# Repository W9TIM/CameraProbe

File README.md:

# CameraProbe

A macOS menu bar utility that watches for camera activity and reacts to it: flips a physical "on air" relay, and/or fires a Home Assistant webhook, whenever your Mac's camera turns on or off.

Ships as a normal `.app` you drag into `/Applications` - no installer, no `sudo`, no LaunchAgent. It lives in the menu bar with a custom tally-light icon, shows a red dot on top of it whenever the camera is actively in use, and everything is configured from a Preferences window.

> **Windows:** a Windows 10/11 tray version (2.0.0, matching this macOS release) lives in [`windows/`](windows/README.md). It uses the same relay firmware, Home Assistant webhooks and config schema. The rest of this README covers the macOS app.

## Features

- Detects camera start/stop by watching the unified log stream for `cameracaptured` events - no polling, no private APIs.
- Reports which application grabbed the camera (Zoom, FaceTime, Photo Booth, Teams, browsers, etc.).
- Controls an HTTP-controlled relay (e.g. an ESP8266/ESP32 running Tasmota or custom firmware) for a physical "on air" light.
- Fires Home Assistant webhooks (`camera_on` / `camera_off`) so you can build automations on top of camera state.
- Menu bar icon shows a red dot the instant CameraProbe itself detects the camera in use by a non-excluded app - a local, independent signal that doesn't depend on the relay or Home Assistant being enabled, configured, or reachable. Goes dark while Inactivate is on.
- Right-click menu: About, Preferences, Inactivate/Reactivate (pause relay + Home Assistant notifications without quitting - camera detection keeps running), Quit.
- Preferences window for relay, Home Assistant, ignored apps, and Start at Login - no manual config-file editing required. Changes apply immediately, no restart.
- `ignoredApplications` exclude list - apps that activate the camera without ever notifying the relay/Home Assistant (privacy, gameplay capture, etc.), editable from Preferences.
- Self-healing: if the underlying log-stream process dies, it restarts automatically with backoff.
- `CameraProbe --test` and `CameraProbe --status` for command-line diagnostics.

## Requirements

- macOS 14 or later.
- Xcode Command Line Tools (to build from source): `xcode-select --install`.
- An HTTP-controlled relay reachable on your LAN (optional - can be disabled in Preferences).
- A Home Assistant instance with webhook automations for `camera_on` / `camera_off` (optional - can be disabled in Preferences).

## Download

Prebuilt installers are on the [**latest release**](https://github.com/W9TIM/CameraProbe/releases/latest) page:

- **macOS:** `CameraProbe.dmg` - open it and drag **CameraProbe** onto **Applications**.
- **Windows:** `CameraProbe-Setup-<version>.exe` - run it (see [`windows/README.md`](windows/README.md#install)).

Neither is signed or notarized, so your OS will warn on first launch - see **First launch** below (macOS) or the Windows README (SmartScreen: **More info → Run anyway**). Prefer to build it yourself? Use the steps below.

## Install (build from source)

```
git clone <this repository>
cd CameraProbe
./build-app.sh
```

This builds the release binary and assembles `dist/CameraProbe.app` (plus `dist/CameraProbe.dmg`). No `sudo` at any point.

Then either:

- Open `dist/CameraProbe.dmg` and drag **CameraProbe** onto the **Applications** shortcut, or
- Drag `dist/CameraProbe.app` straight into `/Applications` in Finder.

**First launch:** the app isn't notarized by Apple, so right-click `CameraProbe.app` in `/Applications` and choose **Open**, then confirm - after that first approval, opening it normally (double-click, Spotlight, login item) works fine. If macOS still refuses, open **System Settings → Privacy & Security**, scroll to the message about CameraProbe, and click **Open Anyway**.

A brief splash screen (showing the app's own tally-light icon) appears, then CameraProbe settles into the menu bar (look for the tally-light icon near the clock - no Dock icon, this is a background utility). The first time it talks to the network, macOS shows a **Local Network** permission prompt - click **Allow**. `build-app.sh` code-signs the app with a stable identifier specifically so this approval survives future rebuilds.

Open the menu bar icon → **Preferences…** to set your relay and Home Assistant hostnames, and optionally turn on **Start at Login**.

See [INSTALL.md](INSTALL.md) for a more detailed walkthrough and troubleshooting.

## Configuration

Preferences window (menu bar icon → **Preferences…**) is the normal way to change settings - relay enabled/host/port, Home Assistant enabled/host/port, ignored applications, and Start at Login. Saving writes to disk and takes effect immediately, no restart needed.

Under the hood, this is stored at `~/Library/Application Support/CameraProbe/config.json`:

```json
{
  "relay": {
    "enabled": true,
    "host": "onair.local",
    "port": 80
  },
  "homeAssistant": {
    "enabled": true,
    "host": "homeassistant.local",
    "port": 8123
  },
  "ignoredApplications": []
}
```

Every field is optional - anything you omit falls back to the default shown above. You can hand-edit this file directly if you prefer (per-user path, no `sudo` needed); CameraProbe doesn't watch it for external changes, though, so use Preferences if the app is already running. A malformed config file is logged as a warning and CameraProbe falls back to defaults rather than failing to start.

**`ignoredApplications`** is an exclude list: every app that activates the camera still triggers a notification by default (empty list), but you can name specific apps to skip - for privacy (e.g. Photo Booth) or gameplay capture you don't want broadcasting "on air". Add them one per line in Preferences, or as a JSON array:

```json
"ignoredApplications": ["Photo Booth", "OBS"]
```

Matching is case-insensitive and uses the same app name CameraProbe logs/reports (`log stream --predicate 'subsystem == "com.tim.cameraprobe"'` will show you the exact name it detected if you're not sure). When an ignored app is what grabbed the camera, neither the relay nor Home Assistant gets notified for that session - including the matching "off" event, so you won't see a stray "camera off" with no preceding "on".

See `config.example.json` for a copyable template.

## Usage

CameraProbe normally just runs in the menu bar, but the same binary supports a few commands directly from Terminal (handy for scripting/troubleshooting):

```
CameraProbe                Launch the menu bar app (splash screen, then runs in the menu bar)
CameraProbe --status       One-shot summary: relay, Home Assistant, Start at Login, camera monitor
CameraProbe --test         Full diagnostics: DNS, relay, Home Assistant, log access, Start at Login
CameraProbe --version      Print the version
CameraProbe --help         Show usage
```

Example `--status` output:

```
CameraProbe 2.0.0

Relay...............OK
Home Assistant......OK
Start at Login......Enabled
Camera Monitor......Running
```

Live logs:

```
log stream --predicate 'subsystem == "com.tim.cameraprobe"'
```

## Uninstall

Turn off **Start at Login** in Preferences first (if you'd enabled it), then quit CameraProbe from the menu bar and drag `CameraProbe.app` from `/Applications` to the Trash. That's it - no installer to run in reverse.

To also remove your saved settings:

```
rm -rf ~/Library/Application\ Support/CameraProbe
```

If you're upgrading from the older LaunchAgent-based install, see the note at the top of [INSTALL.md](INSTALL.md) for how to remove that first.

## How it works

CameraProbe shells out to `/usr/bin/log stream` with a predicate that matches `cameracaptured`'s `DidStartRunning`/`DidStopRunning` events - the same signal macOS's own camera indicator light relies on. When the camera turns on, it waits briefly (to let the capturing app become frontmost), asks `NSWorkspace` which application is active, then notifies the relay and Home Assistant (unless the app is in `ignoredApplications`, or Inactivate is on). When it turns off, both get an "off" notification immediately.

The menu bar's red dot is driven by that same local detection, independently of whether the relay/Home Assistant notifications actually went out: it lights up the instant a non-excluded app grabs the camera, and goes dark the instant the camera is released or Inactivate is toggled on. It never polls or depends on the relay or Home Assistant being enabled, configured, or reachable - it's purely "does CameraProbe itself currently consider the camera in use."

## Relay firmware

The `firmware/` folder has the ESP8266 firmware for the physical relay CameraProbe talks to by default. The recommended **universal firmware** (`CameraProbeRelayUniversal/`) works on either a **Wemos D1 Mini with relay shield** or the more compact **ESP-01S relay module**. You flash it once, then set WiFi and the board type from a web page, either on the device's **ConfigRelay** setup network or at `http://onair.local/configure`. The original fixed-configuration sketches (`CameraProbeRelay/`, `CameraProbeRelay8266/`) are kept as well. See [firmware/README.md](firmware/README.md) for which to choose, wiring, Arduino IDE setup, and flashing instructions. If you already have relay hardware exposing `GET /on` / `GET /off` / `GET /status`, you don't need it; just point the relay host in Preferences (or `config.json`) at your existing device.

The low voltage relay is used for controlling power to a 5V (USB) light (On/Off) via WiFi. The control unit is constructed with a Wemos D1 Mini (ESP8266) with a single relay shield attached.

This can be housed in a simple 3D printable enclosure and mounted near or for shaddow box lights, inside to keep it out of the way. This arrangement will require two USB connections. One to power the Wemos D1 and one to power the light itself, which will be switched on/off when the +5v line is interrupted by the relay shield. 

Photos and 3D-printable files are included with this project:

- **ESP-01S relay case:** a compact two-part enclosure (base and friction-fit lid) - print-ready [STL](firmware/ESP8266%20Module%20Device/ESP01S_Relay_Case.stl), editable [OpenSCAD source](firmware/ESP8266%20Module%20Device/ESP01S_Relay_Case.scad), and the [design spec](firmware/ESP8266%20Module%20Device/CASE_DESIGN_SPEC.md). Includes a single-supply wiring photo and diagram in [firmware/README.md](firmware/README.md#single-supply-wiring-esp-01s-relay-variant).
- **Wemos D1 Mini case:** see the `3D Printable Files` folder under `firmware/`.

## Home Assistant setup

CameraProbe calls two built-in Home Assistant webhooks (`camera_on` / `camera_off`) - see [homeassistant/README.md](homeassistant/README.md) for how to wire those up to an automation, with both a UI walkthrough and a copyable YAML example.

## Project layout

**Sources/CameraProbe/**

| File | Purpose |
|---|---|
| `main.swift` | Entry point: CLI flag parsing, launches the menu bar app |
| `AppDelegate.swift` | App lifecycle: splash screen, signal handling, startup |
| `StatusBarController.swift` | Menu bar icon, right-click menu, camera-activity dot overlay |
| `SettingsWindowController.swift` | Preferences window |
| `SplashWindowController.swift` | Brief launch splash screen (shows the app icon) |
| `PauseState.swift` | Inactivate/Reactivate state |
| `LoginItem.swift` | Start at Login (`SMAppService`) |
| `Configuration.swift` | Config schema, per-user config file, live `ConfigStore` |
| `Logger.swift` | OSLog setup, startup banner |
| `CameraMonitor.swift` | Camera state + log-stream subprocess management |
| `Relay.swift` | Relay HTTP calls |
| `HomeAssistant.swift` | Home Assistant webhook calls |
| `ActiveApplication.swift` | Frontmost-app lookup |
| `Diagnostics.swift` | `--test` / `--status` / `--help` implementation |
| `Utilities.swift` | DNS check |

**Other top-level files and folders**

| Path | Purpose |
|---|---|
| `Package.swift` | Swift package manifest |
| `build-app.sh` | Builds `dist/CameraProbe.app` and `dist/CameraProbe.dmg` |
| `Info.plist.template` | App bundle metadata used by `build-app.sh` |
| `Resources/AppIcon.svg`, `Resources/AppIcon.iconset/` | App icon source and compiled sizes - see "App icon" below |
| `config.example.json` | Copyable config template |
| `firmware/` | ESP8266 relay sketch, wiring docs, WiFi credentials template |
| `homeassistant/` | Home Assistant automation setup docs and example YAML |
| `windows/` | The Windows tray app (C#/.NET 8) - see [`windows/README.md`](windows/README.md) |
| `WINDOWS_PORT.md` | Windows port plan and camera-detection test findings |
| `install.sh`, `uninstall.sh`, `com.tim.cameraprobe.plist.template` | Legacy LaunchAgent installer - superseded by `build-app.sh`, kept for reference |
| `README.md`, `INSTALL.md`, `CHANGELOG.md`, `LICENSE` | Project docs |

## App icon

The icon is a custom "tally light" design - a camera lens with a glowing red indicator and an ON AIR badge, matching the menu bar's own activity dot visually. Source files live under `Resources/`:

- `Resources/AppIcon.svg` - the editable vector source.
- `Resources/AppIcon.iconset/` - the 10 PNG sizes Apple requires, generated from the SVG.

`build-app.sh` compiles the iconset into `AppIcon.icns` via `iconutil` (bundled with Xcode) and embeds it in `CameraProbe.app/Contents/Resources/`, referenced from `Info.plist.template`'s `CFBundleIconFile`. It also stamps the same icon onto `dist/CameraProbe.dmg` as the disk image's own volume icon (via `SetFile`, skipped with a warning if that tool isn't installed - the app's icon isn't affected either way). The splash screen shown at launch displays this same icon (`NSApp.applicationIconImage`), falling back to a generic system icon only when running unbundled (e.g. `swift run` during development, before Info.plist's icon applies).

To change the artwork: edit or regenerate `Resources/AppIcon.svg`, re-render it to the 10 PNG sizes listed in `Resources/AppIcon.iconset/`, and run `./build-app.sh` again - no other changes needed.

## Troubleshooting

**macOS says the app "can't be opened because it is from an unidentified developer."** Right-click (not double-click) `CameraProbe.app` in `/Applications` and choose **Open**, then confirm in the dialog. This is only needed once - it's Gatekeeper reacting to an ad-hoc-signed, non-notarized app, not a sign of a broken build.

**Local Network permission dialog reappears after a rebuild.** This means the app's signature changed. `build-app.sh` re-signs it with a fixed identifier each time specifically to prevent this - make sure you're rebuilding via `./build-app.sh` rather than copying the binary manually.

**Preferences changes don't seem to apply.** They take effect immediately in the running app - no restart needed. If it still looks stale, confirm you clicked **Save** (not the titlebar close button), and check `~/Library/Application Support/CameraProbe/config.json`'s contents directly.

**Nothing happens when the camera turns on.** Run `CameraProbe --test` (from Terminal: `/Applications/CameraProbe.app/Contents/MacOS/CameraProbe --test`) to check each subsystem individually, and `log stream --predicate 'subsystem == "com.tim.cameraprobe"'` to watch live logs while triggering the camera (e.g. open Photo Booth). Also check the menu bar icon isn't showing "Inactivate" as reversed to "Reactivate" (meaning notifications are currently paused).

**Upgrading from the old LaunchAgent-based install.** See the note at the top of [INSTALL.md](INSTALL.md) - remove the LaunchAgent first to avoid two copies of CameraProbe running at once.

## License

MIT - see [LICENSE](LICENSE).

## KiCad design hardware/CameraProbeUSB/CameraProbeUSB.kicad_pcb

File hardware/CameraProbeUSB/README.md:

# CameraProbe USB Relay Board (Rev A)

> **Status: paused (October 2026).** This design is complete and routed (DRC clean, Gerbers in `Gerbers/`) but has **not been built or tested**. Development stopped because the per-unit cost in small quantities is higher than the ESP-01S relay module or an off-the-shelf USB switch running the universal firmware (see `firmware/README.md`). The files are kept for reference; if you build one, treat it as untested.

A USB stick with a USB-A plug in, a switched USB-A socket out, and an ESP-12F inside. It runs the universal relay firmware and is programmed through its own USB plug. The full circuit, parts list, layout rules and bring-up steps are in [DESIGN.md](DESIGN.md).

## Files

| File | What it is |
|---|---|
| `DESIGN.md` | The design spec (start here) |
| `CameraProbeUSB.kicad_pro` | KiCad project: open this |
| `CameraProbeUSB.kicad_sch` | Schematic, generated from the spec |
| `CameraProbeUSB.net` | Netlist (backup way into the PCB editor) |
| `tools/generate_kicad.py` | Script that generates the schematic and netlist from one circuit table |

## Opening it in KiCad (8 or 9)

1. **File → Open Project…** and choose `CameraProbeUSB.kicad_pro`.
2. Open the **Schematic Editor**. The sheet is grouped into five labelled blocks (USB input and regulator, USB serial, ESP-12F, output switch, optional LED). Parts are simple labelled boxes, and connections are made with **net labels**: two pins with the same label (e.g. `+3V3`) are connected.
3. Run **Inspect → Electrical Rules Checker**. It should report no errors.
4. **USB connectors:** the footprints match two specific parts, so buy exactly these: J1 = **CNC Tech 1001-011-01101** (USB-A plug, Digi-Key 1175-1008-ND) and J2 = **Molex 0676433910** (USB-A socket). Every other part has a hand-solder footprint from KiCad's standard libraries.
5. Check the **ESP-12F GPIO4 / GPIO5 pins** (pins 19 and 20) against your module's datasheet. Some ESP-12 modules have these two swapped. If yours does, either swap the `BTN` / `SW_DRV` labels on U3, or keep the board and choose **Custom → GPIO4** in the firmware setup page.
6. **Tools → Update PCB from Schematic** (F8) sends everything to the PCB editor for layout. Follow the layout guidelines in DESIGN.md section 4.

If the schematic won't open for any reason, you can still start the layout: open the **PCB Editor** → **File → Import → Netlist…** → choose `CameraProbeUSB.net`.

## Changing the circuit

Edit the `CIRCUIT` table in `tools/generate_kicad.py`, then run:

```
python3 hardware/CameraProbeUSB/tools/generate_kicad.py
```

This regenerates the schematic and netlist. **Regenerating overwrites the schematic**, so once you start editing the schematic by hand in KiCad (moving parts, assigning footprints), make further changes in KiCad and stop using the script.

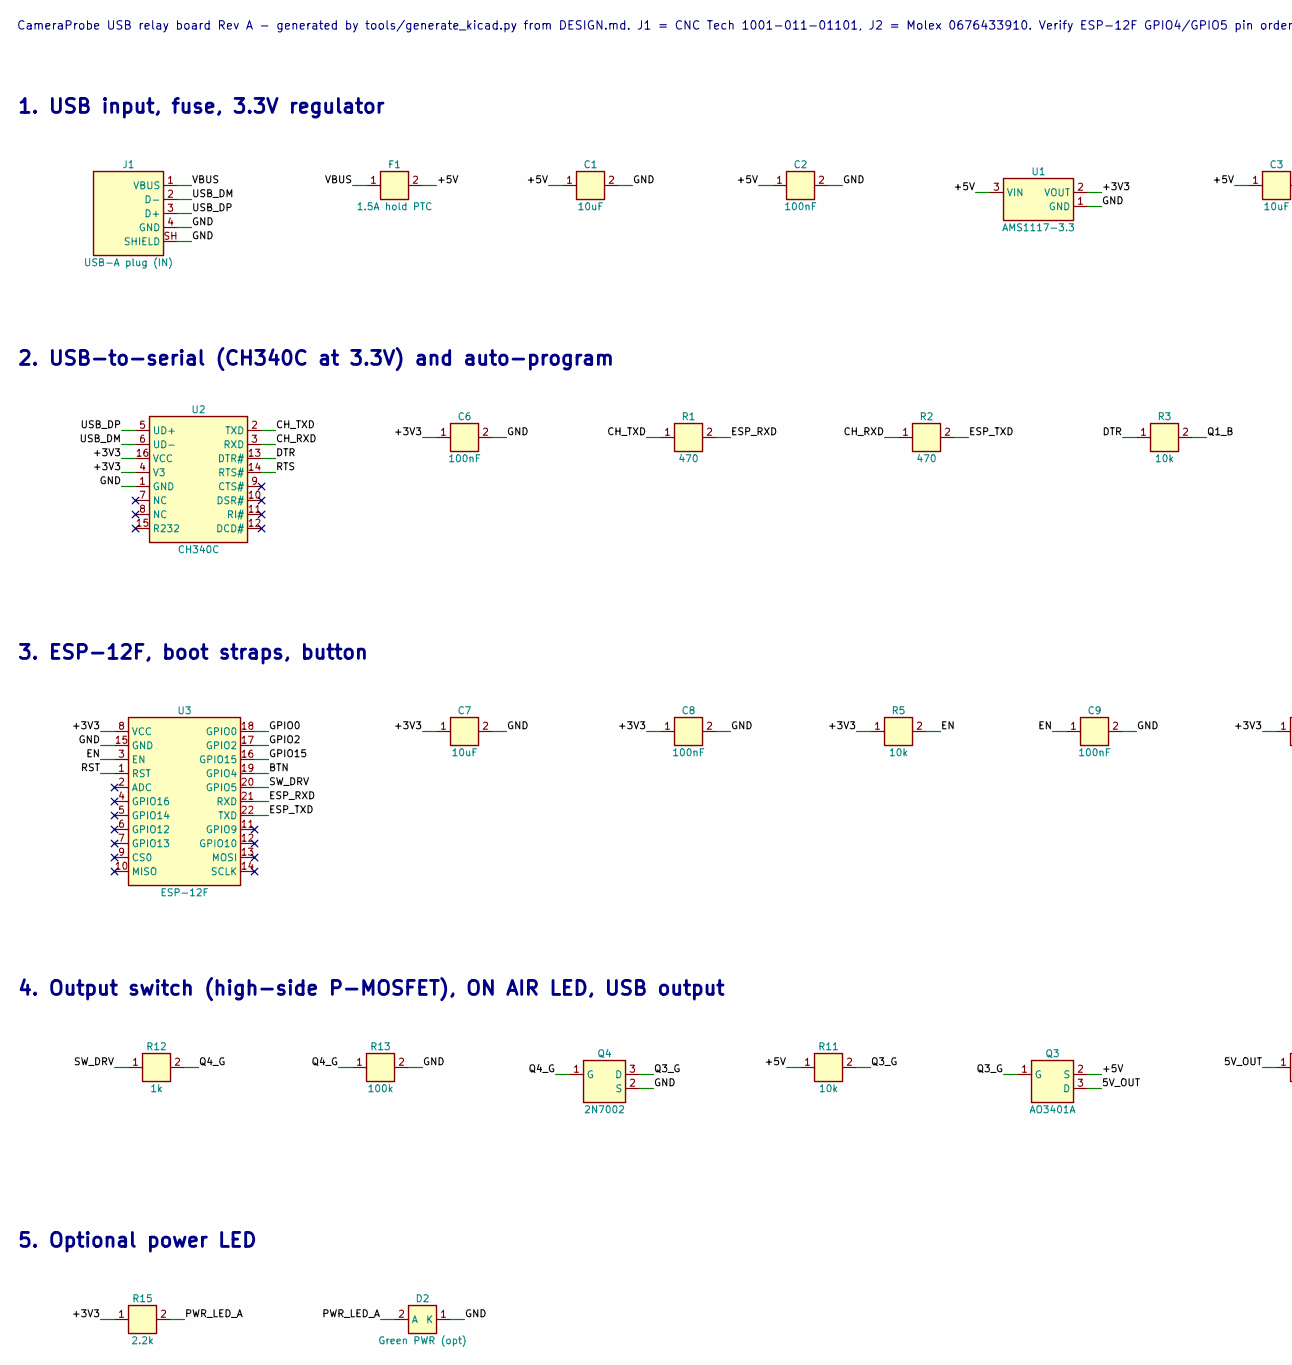
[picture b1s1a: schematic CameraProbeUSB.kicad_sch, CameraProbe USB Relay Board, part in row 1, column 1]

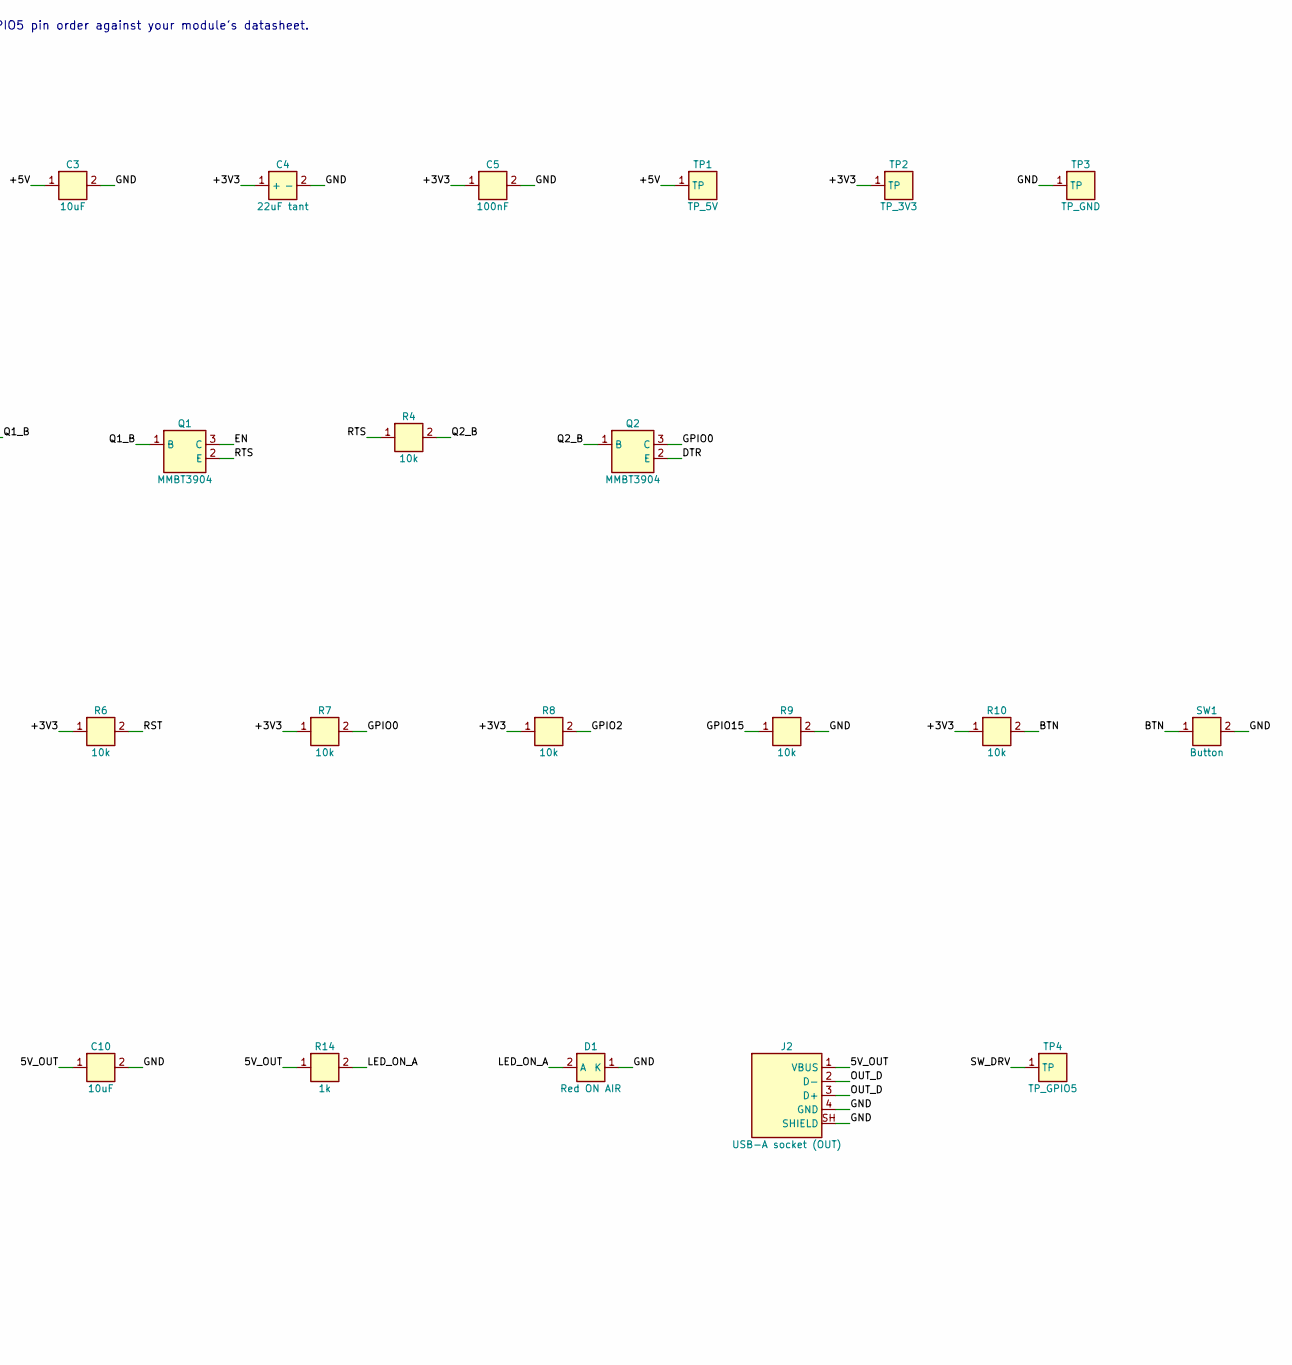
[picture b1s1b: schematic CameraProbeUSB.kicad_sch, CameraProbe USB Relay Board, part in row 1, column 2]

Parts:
C1, C3, C7, C10: 10uF; C_0805_2012Metric_Pad1.18x1.45mm_HandSolder
C2, C5, C6, C8, C9: 100nF; C_0805_2012Metric_Pad1.18x1.45mm_HandSolder
C4: 22uF tant; CP_EIA-3216-18_Kemet-A
D1: Red ON AIR; LED_0805_2012Metric_Pad1.15x1.40mm_HandSolder
D2: Green PWR (opt); LED_0805_2012Metric_Pad1.15x1.40mm_HandSolder
F1: 1.5A hold PTC; Fuse_1812_4532Metric
J1: USB-A plug (IN); USB_A_CNCTech_1001-011-01101_Horizontal
J2: USB-A socket (OUT); USB_A_Molex_67643_Horizontal
Q1, Q2: MMBT3904; SOT-23
Q3: AO3401A; SOT-23
Q4: 2N7002; SOT-23
R1, R2: 470; R_0805_2012Metric_Pad1.20x1.40mm_HandSolder
R3, R4, R5, R6, R7, R8, R9, R10, R11: 10k; R_0805_2012Metric_Pad1.20x1.40mm_HandSolder
R12, R14: 1k; R_0805_2012Metric_Pad1.20x1.40mm_HandSolder
R13: 100k; R_0805_2012Metric_Pad1.20x1.40mm_HandSolder
R15: 2.2k; R_0805_2012Metric_Pad1.20x1.40mm_HandSolder
SW1: Button; SW_PUSH_6mm
TP1: TP_5V; TestPoint_Pad_D1.5mm
TP2: TP_3V3; TestPoint_Pad_D1.5mm
TP3: TP_GND; TestPoint_Pad_D1.5mm
TP4: TP_GPIO5; TestPoint_Pad_D1.5mm
U1: AMS1117-3.3; SOT-223-3_TabPin2
U2: CH340C; SOIC-16_3.9x9.9mm_P1.27mm
U3: ESP-12F; ESP-12E

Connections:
/5V_OUT: C10.1, J2.1 (VBUS), Q3.3 (D), R14.1
/+3V3: C4.1 (+), C5.1, C6.1, C7.1, C8.1, R5.1, R6.1, R7.1, R8.1, R10.1, R15.1, TP2.1 (TP_1), U1.2 (VOUT), U2.4 (V3), U2.16 (VCC), U3.8 (VCC)
/+5V: C1.1, C2.1, C3.1, F1.2, Q3.2 (S), R11.1, TP1.1 (TP_1), U1.3 (VIN)
/BTN: R10.2, SW1.1, U3.19 (GPIO4)
/CH_RXD: R2.1, U2.3 (RXD)
/CH_TXD: R1.1, U2.2 (TXD)
/DTR: Q2.2 (E), R3.1, U2.13 (DTR#)
/EN: C9.1, Q1.3 (C), R5.2, U3.3 (EN)
/ESP_RXD: R1.2, U3.21 (RXD)
/ESP_TXD: R2.2, U3.22 (TXD)
/GND: C1.2, C2.2, C3.2, C4.2 (-), C5.2, C6.2, C7.2, C8.2, C9.2, C10.2, D1.1 (K), D2.1 (K), J1.4 (GND), J1.SH (SHIELD), J2.4 (GND), J2.SH (SHIELD), Q4.2 (S), R9.2, R13.2, SW1.2, TP3.1 (TP_1), U1.1 (GND), U2.1 (GND), U3.15 (GND)
/GPIO0: Q2.3 (C), R7.2, U3.18 (GPIO0)
/GPIO2: R8.2, U3.17 (GPIO2)
/GPIO15: R9.1, U3.16 (GPIO15)
/LED_ON_A: D1.2 (A), R14.2
/OUT_D: J2.2 (D-), J2.3 (D+)
/PWR_LED_A: D2.2 (A), R15.2
/Q1_B: Q1.1 (B), R3.2
/Q2_B: Q2.1 (B), R4.2
/Q3_G: Q3.1 (G), Q4.3 (D), R11.2
/Q4_G: Q4.1 (G), R12.2, R13.1
/RST: R6.2, U3.1 (RST)
/RTS: Q1.2 (E), R4.1, U2.14 (RTS#)
/SW_DRV: R12.1, TP4.1 (TP_1), U3.20 (GPIO5)
/USB_DM: J1.2 (D-), U2.6 (UD-)
/USB_DP: J1.3 (D+), U2.5 (UD+)
/VBUS: F1.1, J1.1 (VBUS)

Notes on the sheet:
1. USB input, fuse, 3.3V regulator
2. USB-to-serial (CH340C at 3.3V) and auto-program
3. ESP-12F, boot straps, button
4. Output switch (high-side P-MOSFET), ON AIR LED, USB output
5. Optional power LED
CameraProbe USB relay board Rev A - generated by tools/generate_kicad.py from DESIGN.md. J1 = CNC Tech 1001-011-01101, J2 = Molex 0676433910. Verify ESP-12F GPIO4/GPIO5 pin order against your module's datasheet.

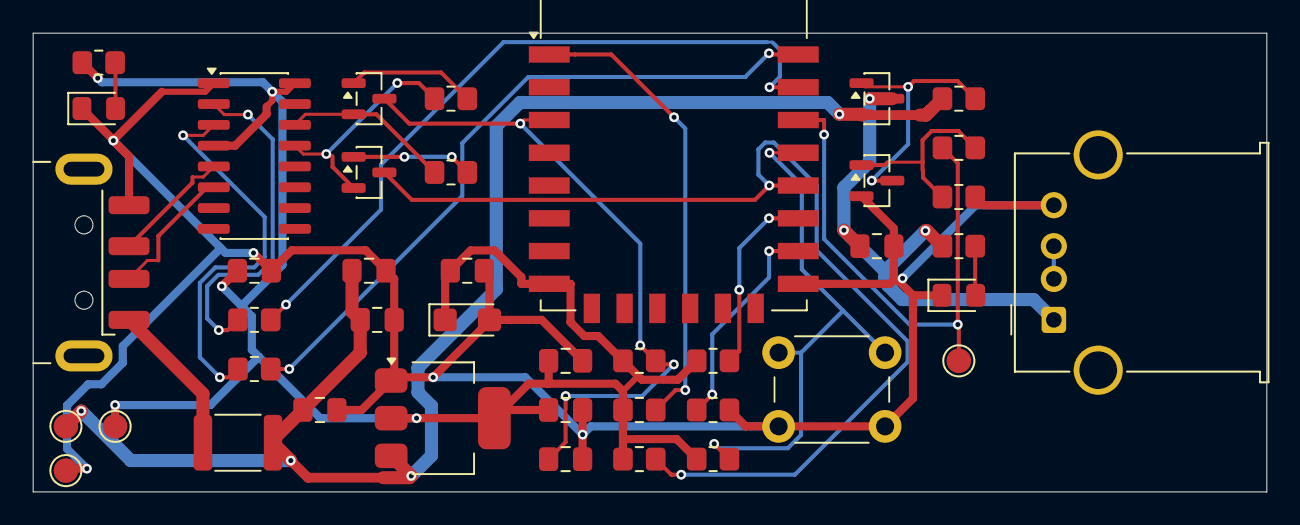
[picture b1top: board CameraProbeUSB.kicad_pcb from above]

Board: 2 copper layers, 75.3 x 28.0 mm, 42 parts (0 on the bottom side), 27 nets.

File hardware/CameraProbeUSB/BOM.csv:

Qty per board,Order qty (5 boards + spares),References,Description,Package,Manufacturer part number,Where to buy,Notes
1,6,U3,ESP-12F WiFi module (ESP8266),castellated module,Ai-Thinker ESP-12F,Amazon (search "ESP-12F"),Not usually stocked by Digi-Key
1,6,U2,CH340C USB-to-serial,SOIC-16,WCH CH340C,Amazon / LCSC (search "CH340C SOIC-16"),Must be the C variant (no crystal needed)
1,6,U1,AMS1117-3.3 regulator 1A,SOT-223,TI LM1117MPX-3.3/NOPB (or AMS1117-3.3),Digi-Key,"Same SOT-223 pinout (1 GND, 2 OUT, 3 IN)"
2,12,Q1 Q2,NPN transistor,SOT-23,MMBT3904,Digi-Key,
1,6,Q3,P-channel MOSFET,SOT-23,Vishay SI2301CDS-T1-BE3 (or AO3401A),Digi-Key,"Pinout G=1 S=2 D=3; Vgs max 8V is fine at 5V"
1,6,Q4,N-channel MOSFET,SOT-23,2N7002,Digi-Key,
1,6,F1,Polyfuse 1.5A hold,1812,Bourns MF-MSMF150,Digi-Key,Any 1812 PTC with ~1.5A hold
1,6,J1,USB-A plug right angle PCB,SMD + THT tabs,CNC Tech 1001-011-01101,Digi-Key (1175-1008-ND),Footprint matches this exact part
1,6,J2,USB-A socket right angle THT,THT,Molex 0676433910,Digi-Key,Footprint matches this exact part
1,6,SW1,Tactile switch 6x6mm THT,THT,Omron B3F-1000 (or any 6x6mm 4-pin),Digi-Key,
1,10,D1,Red LED,0805,any red 0805 LED,Digi-Key / Amazon,
1,10,D2,Green LED (optional power LED),0805,any green 0805 LED,Digi-Key / Amazon,Leave off if you prefer it dark
4,25,C1 C3 C7 C10,10uF 16V X5R/X7R ceramic,0805,Samsung CL21A106KACLRNC (any 10uF 16V+ 0805),Digi-Key,
1,6,C4,22uF 10V tantalum,3216 (A case),any 22uF 10V A-case tantalum,Digi-Key,Mind polarity: stripe = +
5,30,C2 C5 C6 C8 C9,100nF 50V X7R ceramic,0805,any 100nF 0805,Digi-Key,
2,12,R1 R2,470 ohm,0805,Stackpole RMCF0805JT470R (any 470R 0805),Digi-Key,
9,50,R3 R4 R5 R6 R7 R8 R9 R10 R11,10k ohm,0805,any 10k 0805,Digi-Key,
2,12,R12 R14,1k ohm,0805,any 1k 0805,Digi-Key,
1,6,R13,100k ohm,0805,any 100k 0805,Digi-Key,
1,6,R15,2.2k ohm (optional power LED),0805,any 2.2k 0805,Digi-Key,

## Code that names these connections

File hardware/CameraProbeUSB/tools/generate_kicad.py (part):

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                       ("1", "RST", "L"), ("2", "ADC", "L"), ("4", "GPIO16", "L"),
                       ("5", "GPIO14", "L"), ("6", "GPIO12", "L"), ("7", "GPIO13", "L"),
                       ("9", "CS0", "L"), ("10", "MISO", "L"),
                       ("18", "GPIO0", "R"), ("17", "GPIO2", "R"), ("16", "GPIO15", "R"),
                       ("19", "GPIO4", "R"), ("20", "GPIO5", "R"), ("21", "RXD", "R"),
                       ("22", "TXD", "R"), ("11", "GPIO9", "R"), ("12", "GPIO10", "R"),
                       ("13", "MOSI", "R"), ("14", "SCLK", "R")]),
}
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        ("R3", "R", "10k", FP_R, {"1": "DTR", "2": "Q1_B"}),
        ("Q1", "NPN", "MMBT3904", FP_SOT23, {"1": "Q1_B", "2": "RTS", "3": "EN"}),
        ("R4", "R", "10k", FP_R, {"1": "RTS", "2": "Q2_B"}),
        ("Q2", "NPN", "MMBT3904", FP_SOT23, {"1": "Q2_B", "2": "DTR", "3": "GPIO0"}),
    ]),
    ("3. ESP-12F, boot straps, button", [
        ("U3", "ESP12F", "ESP-12F", FP_ESP, {
            "8": "+3V3", "15": "GND", "3": "EN", "1": "RST",
            "2": NC, "4": NC, "5": NC, "6": NC, "7": NC, "9": NC, "10": NC,
            "18": "GPIO0", "17": "GPIO2", "16": "GPIO15", "19": "BTN",
            "20": "SW_DRV", "21": "ESP_RXD", "22": "ESP_TXD",
            "11": NC, "12": NC, "13": NC, "14": NC}),
        ("C7", "C", "10uF", FP_C, {"1": "+3V3", "2": "GND"}),
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        ("R5", "R", "10k", FP_R, {"1": "+3V3", "2": "EN"}),
        ("C9", "C", "100nF", FP_C, {"1": "EN", "2": "GND"}),
        ("R6", "R", "10k", FP_R, {"1": "+3V3", "2": "RST"}),
        ("R7", "R", "10k", FP_R, {"1": "+3V3", "2": "GPIO0"}),
        ("R8", "R", "10k", FP_R, {"1": "+3V3", "2": "GPIO2"}),
        ("R9", "R", "10k", FP_R, {"1": "GPIO15", "2": "GND"}),
        ("R10", "R", "10k", FP_R, {"1": "+3V3", "2": "BTN"}),
        ("SW1", "SW", "Button", FP_SW, {"1": "BTN", "2": "GND"}),
    ]),
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        ("R14", "R", "1k", FP_R, {"1": "5V_OUT", "2": "LED_ON_A"}),
        ("D1", "LED", "Red ON AIR", FP_LED, {"2": "LED_ON_A", "1": "GND"}),
        ("J2", "USB_A", "USB-A socket (OUT)", FP_USB_SOCKET, {"1": "5V_OUT", "2": "OUT_D", "3": "OUT_D", "4": "GND", "SH": "GND"}),
        ("TP4", "TP", "TP_GPIO5", FP_TP, {"1": "SW_DRV"}),
    ]),
    ("5. Optional power LED", [
        ("R15", "R", "2.2k", FP_R, {"1": "+3V3", "2": "PWR_LED_A"}),
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
    notes = ("CameraProbe USB relay board Rev A - generated by tools/generate_kicad.py from DESIGN.md. "
             "J1 = CNC Tech 1001-011-01101, J2 = Molex 0676433910. "
             "Verify ESP-12F GPIO4/GPIO5 pin order against your module's datasheet.")
    items.append(f'(text "{notes}" (exclude_from_sim no) (at 20.32 15.24 0) '
                 f'(effects (font (size 1.524 1.524)) (justify left bottom)) (uuid "{uid()}"))')

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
